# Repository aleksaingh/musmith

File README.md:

# MuSmith
MuSmith is like a mini music controller that obviously can control music (previous track, pause/play, next track) it also has a rotary encoder and an oled screen. For the buttons it has mechanical switches.

## Difficulties
For the difficulties i was pretty much the same as my last project [Clicksmith](https://github.com/aleksaingh/clicksmith). The case in Fusion 360 was really messing with me, I spent a good time with designing it.

## Features:
  + Fully 3D printed case
  + 3 Keys
  + A rotary encoder
  + And a 0.91" oled screen
## Firmware
The firmware is a custom circuitpython script (That I and AI made) and a janky Powershell script (This one AI made) that runs at startup. Why? Because i couldn't think of a better way to capture the song and the artist to display on the OLED. The rotary encoder controls the volume and the keys as said in the begining go to the previous track - play/pause - go to the next track.

## OLED screen
As i said the oled is a 0.91" screen that displays the current song and the artist. If i really want it i will maybe add the current time and the progress bar also.

## BOM
What's needed to make this
  + 1x case (2 3D printed parts)
  + 4x M3x5x4 heatset inserts
  + 4x M3x16 screws
  + 3x Cherry MX Switches
  + 3x Cherry DSA keycaps
  + 1x EC11 Rotary encoder
  + 1x XIAO RP2040
  + 1x 0.91" OLED

That's All! 👋

# Images and other nerdy stuff

## CAD

Case was made in Fusion 360.

The top and bottom halves of the case fit together using four heatset inserts and four M3 Screws.

## PCB

The PCB was made in KiCad pretty fast.

## Schematic

## Credits
Thank you [DinoMito1](https://github.com/DinoMito1) for giving me inpso for the readme (some parts i stole and changed but we don't talk about that)

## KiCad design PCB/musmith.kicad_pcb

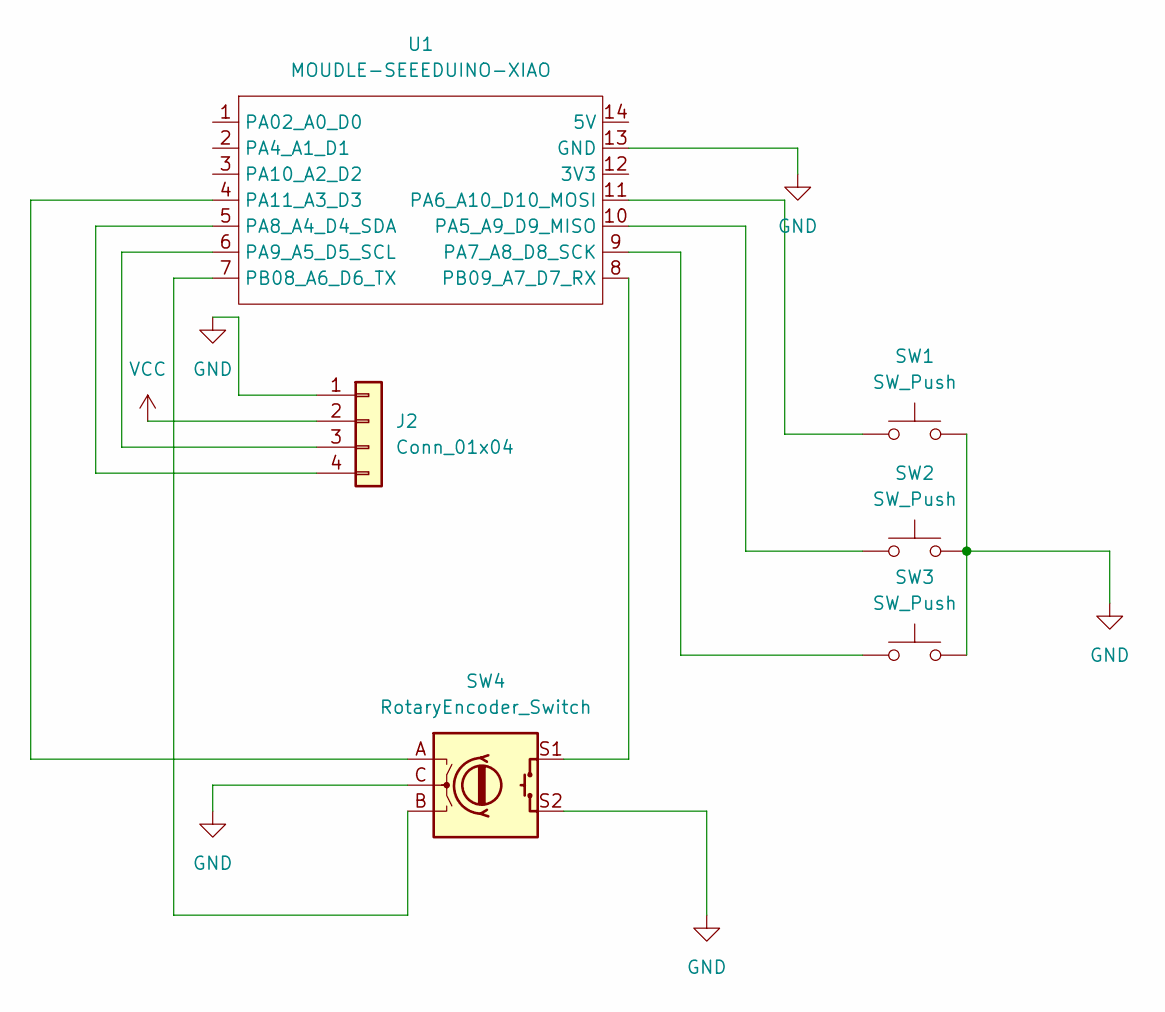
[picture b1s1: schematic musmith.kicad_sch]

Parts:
J2: Conn_01x04; SSD1306-0.91-OLED-4pin-128x32
SW1, SW2, SW3: SW_Push; SW_Cherry_MX_1.00u_PCB
SW4: RotaryEncoder_Switch; RotaryEncoder_Alps_EC11E-Switch_Vertical_H20mm
U1: MOUDLE-SEEEDUINO-XIAO; XIAO-RP2040-DIP

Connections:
GND: J2.1, SW1.2, SW2.2, SW3.2, SW4.C, SW4.S2, U1.13 (GND)
unnamed: J2.3, U1.6 (PA9_A5_D5_SCL)
unnamed: J2.4, U1.5 (PA8_A4_D4_SDA)
unnamed: SW2.1, U1.10 (PA5_A9_D9_MISO)
unnamed: SW1.1, U1.11 (PA6_A10_D10_MOSI)
unnamed: SW3.1, U1.9 (PA7_A8_D8_SCK)
unnamed: SW4.A, U1.4 (PA11_A3_D3)
unnamed: SW4.B, U1.7 (PB08_A6_D6_TX)
unnamed: SW4.S1, U1.8 (PB09_A7_D7_RX)
VCC: J2.2

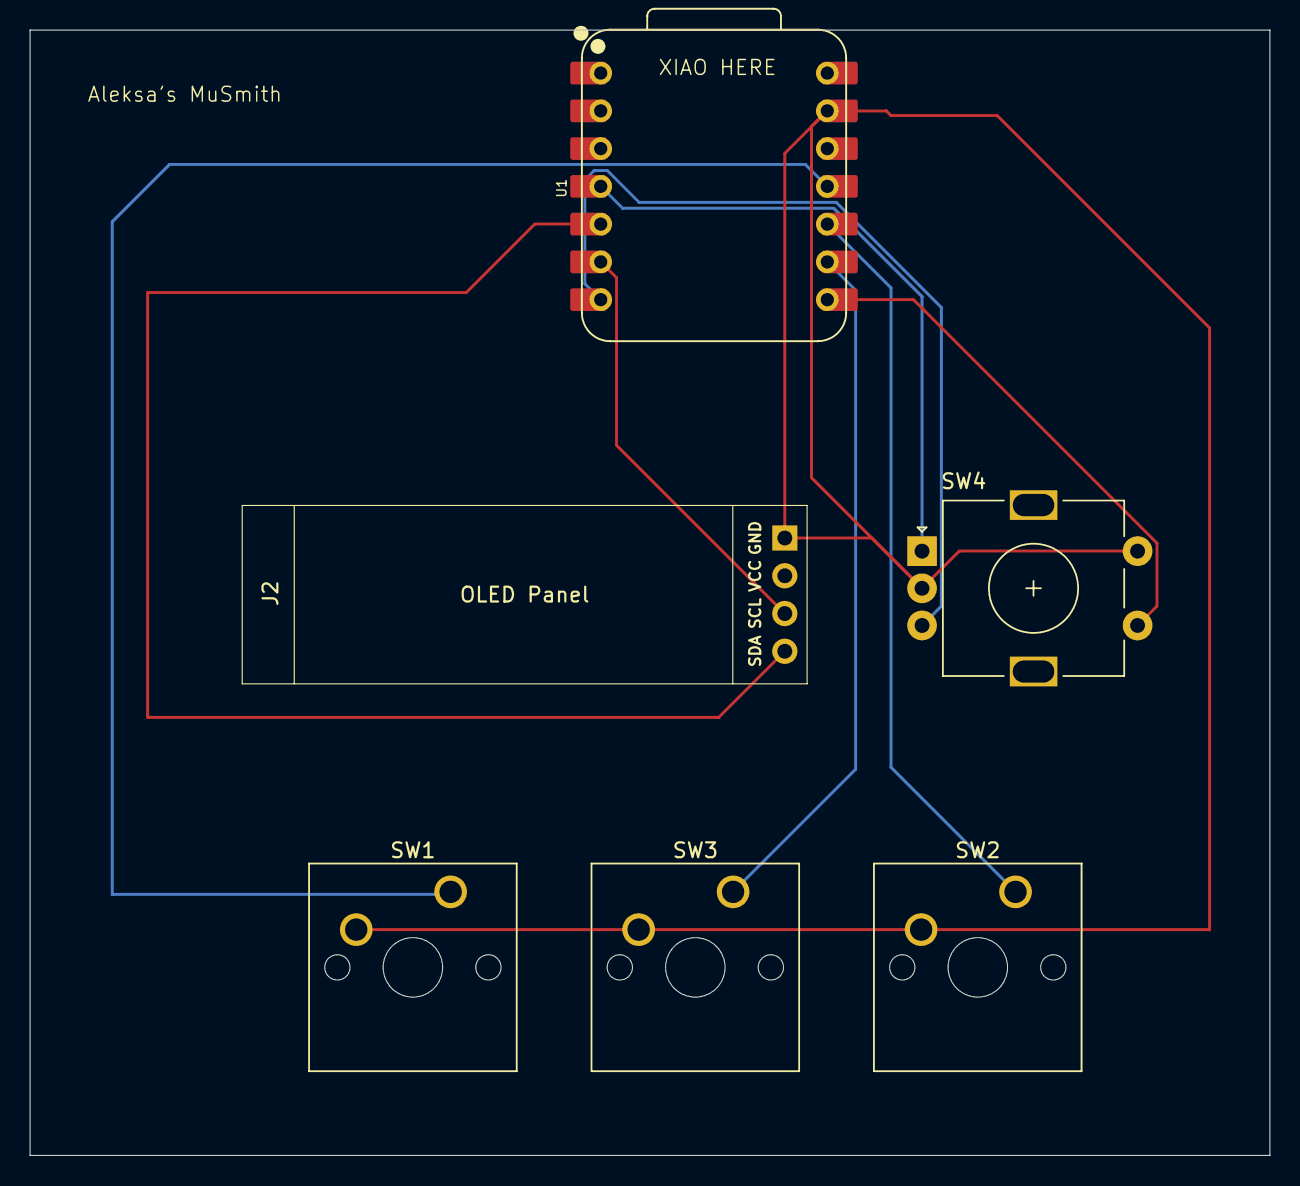
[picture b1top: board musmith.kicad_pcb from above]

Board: 2 copper layers, 83.4 x 75.7 mm, 6 parts (0 on the bottom side), 9 nets.

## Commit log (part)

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2026-06-05 Initial commit: Added CAD, Firmware, and PCB project structures
